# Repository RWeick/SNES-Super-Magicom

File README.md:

# SNES-Super-Magicom
The Kicad files for the SNES Super Magicom

PCB Thicknesses: 
Mainboard - 1.6 mm
RAM Board - 1.6 mm
System Connector Board - 1.2 mm

The system connector board has been modified to allow for the HiROM mod to be installed. Jumpers are labeled to facilitate operation with or without the mod.

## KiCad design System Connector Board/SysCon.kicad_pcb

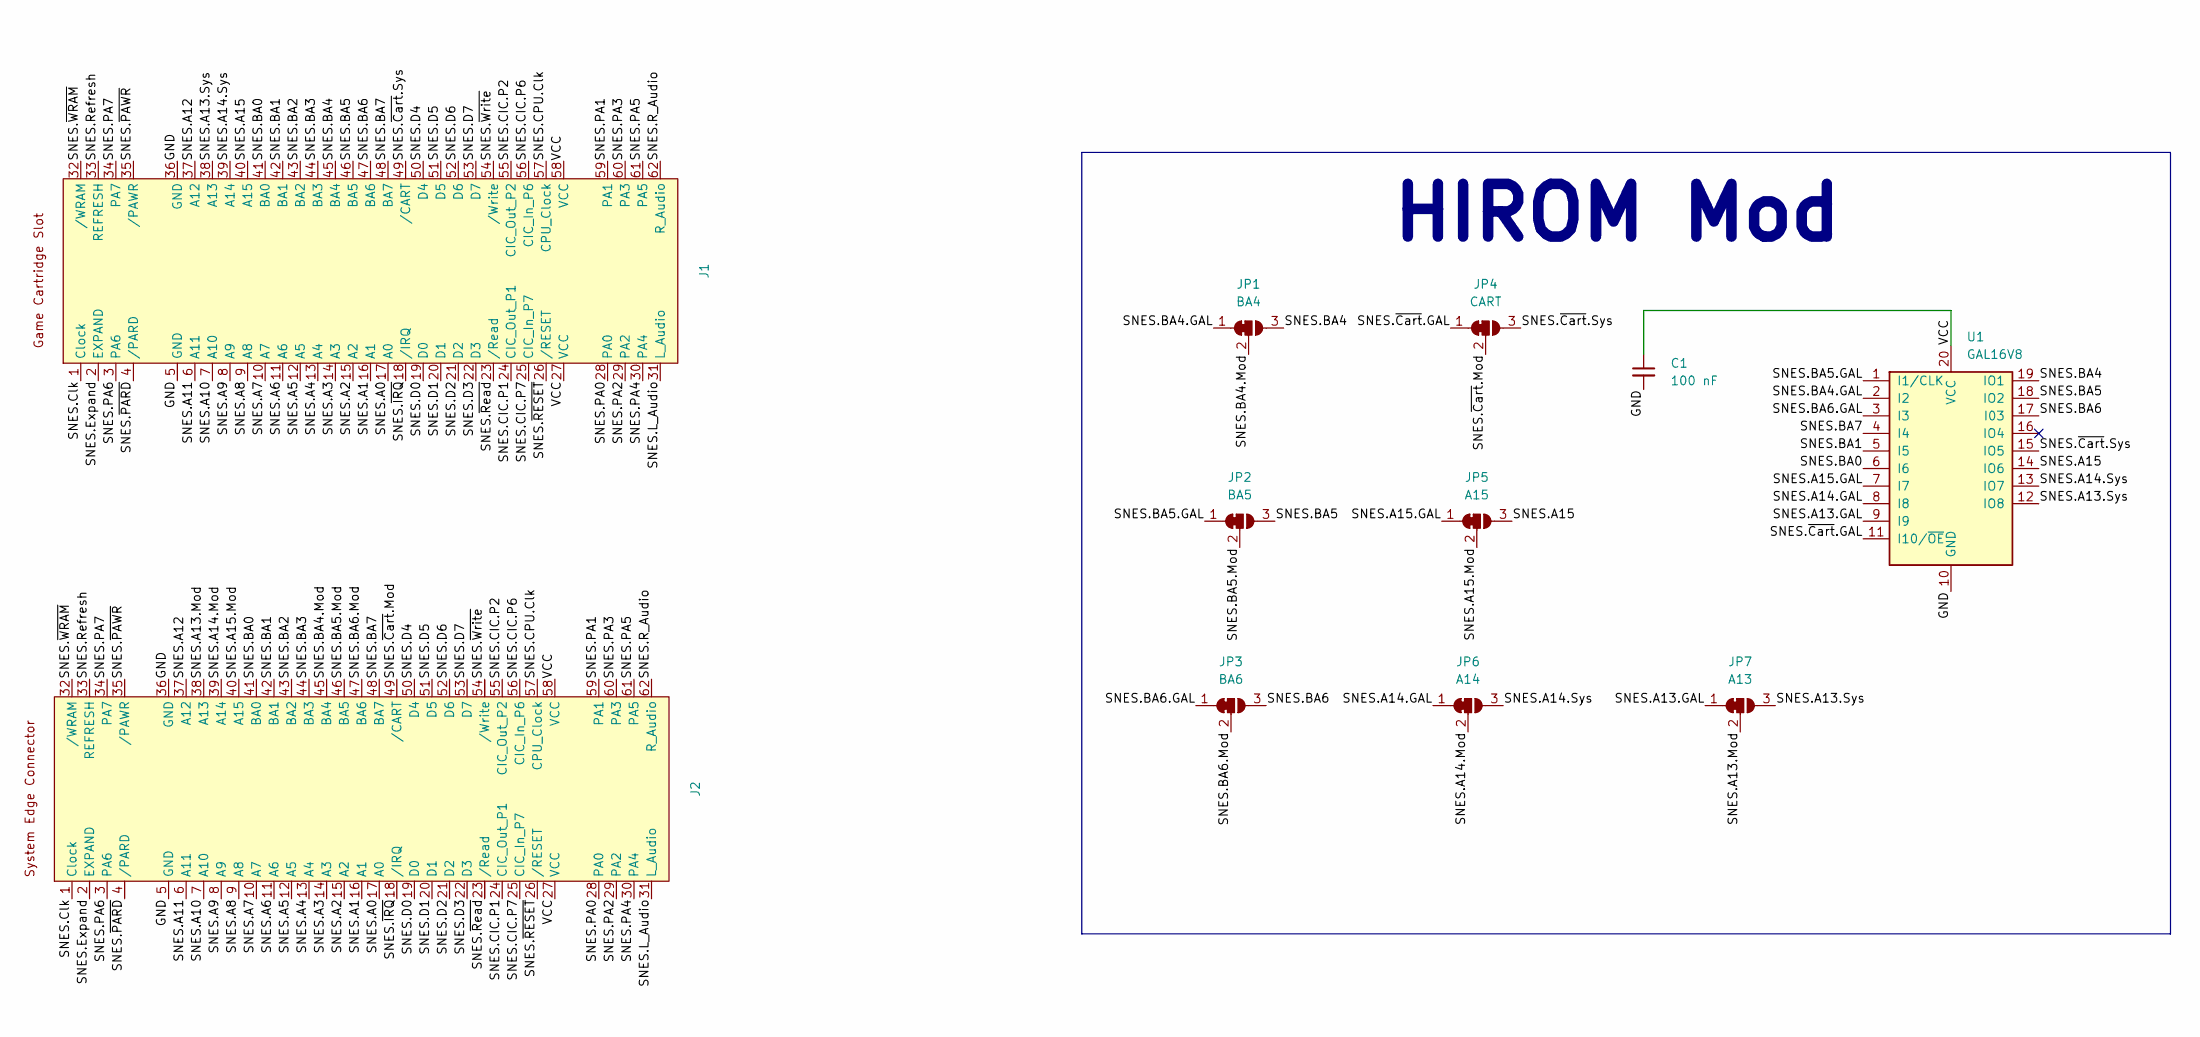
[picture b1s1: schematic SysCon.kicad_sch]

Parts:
C1: 100 nF; C_Disc_D4.3mm_W1.9mm_P5.00mm
J1: Top Connector
J2: Bottom Connector
JP1: BA4; SolderJumper-3_P1.3mm_Open_RoundedPad1.0x1.5mm_NumberLabels
JP2: BA5; SolderJumper-3_P1.3mm_Open_RoundedPad1.0x1.5mm_NumberLabels
JP3: BA6; SolderJumper-3_P1.3mm_Open_RoundedPad1.0x1.5mm_NumberLabels
JP4: CART; SolderJumper-3_P1.3mm_Open_RoundedPad1.0x1.5mm_NumberLabels
JP5: A15; SolderJumper-3_P1.3mm_Open_RoundedPad1.0x1.5mm_NumberLabels
JP6: A14; SolderJumper-3_P1.3mm_Open_RoundedPad1.0x1.5mm_NumberLabels
JP7: A13; SolderJumper-3_P1.3mm_Open_RoundedPad1.0x1.5mm_NumberLabels
U1: GAL16V8; DIP-20_W7.62mm

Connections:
/GND: C1.2, J1.5 (GND), J1.36 (GND), J2.5 (GND), J2.36 (GND), U1.10 (GND)
/SNES.A0: J1.17 (A0), J2.17 (A0)
/SNES.A1: J1.16 (A1), J2.16 (A1)
/SNES.A2: J1.15 (A2), J2.15 (A2)
/SNES.A3: J1.14 (A3), J2.14 (A3)
/SNES.A4: J1.13 (A4), J2.13 (A4)
/SNES.A5: J1.12 (A5), J2.12 (A5)
/SNES.A6: J1.11 (A6), J2.11 (A6)
/SNES.A7: J1.10 (A7), J2.10 (A7)
/SNES.A8: J1.9 (A8), J2.9 (A8)
/SNES.A9: J1.8 (A9), J2.8 (A9)
/SNES.A10: J1.7 (A10), J2.7 (A10)
/SNES.A11: J1.6 (A11), J2.6 (A11)
/SNES.A12: J1.37 (A12), J2.37 (A12)
/SNES.A13.GAL: JP7.1 (A), U1.9 (I9)
/SNES.A13.Mod: J2.38 (A13), JP7.2 (C)
/SNES.A13.Sys: J1.38 (A13), JP7.3 (B), U1.12 (IO8)
/SNES.A14.GAL: JP6.1 (A), U1.8 (I8)
/SNES.A14.Mod: J2.39 (A14), JP6.2 (C)
/SNES.A14.Sys: J1.39 (A14), JP6.3 (B), U1.13 (IO7)
/SNES.A15: J1.40 (A15), JP5.3 (B), U1.14 (IO6)
/SNES.A15.GAL: JP5.1 (A), U1.7 (I7)
/SNES.A15.Mod: J2.40 (A15), JP5.2 (C)
/SNES.BA0: J1.41 (BA0), J2.41 (BA0), U1.6 (I6)
/SNES.BA1: J1.42 (BA1), J2.42 (BA1), U1.5 (I5)
/SNES.BA2: J1.43 (BA2), J2.43 (BA2)
/SNES.BA3: J1.44 (BA3), J2.44 (BA3)
/SNES.BA4: J1.45 (BA4), JP1.3 (B), U1.19 (IO1)
/SNES.BA4.GAL: JP1.1 (A), U1.2 (I2)
/SNES.BA4.Mod: J2.45 (BA4), JP1.2 (C)
/SNES.BA5: J1.46 (BA5), JP2.3 (B), U1.18 (IO2)
/SNES.BA5.GAL: JP2.1 (A), U1.1 (I1/CLK)
/SNES.BA5.Mod: J2.46 (BA5), JP2.2 (C)
/SNES.BA6: J1.47 (BA6), JP3.3 (B), U1.17 (I03)
/SNES.BA6.GAL: JP3.1 (A), U1.3 (I3)
/SNES.BA6.Mod: J2.47 (BA6), JP3.2 (C)
/SNES.BA7: J1.48 (BA7), J2.48 (BA7), U1.4 (I4)
/SNES.CIC.P1: J1.24 (CIC_Out_P1), J2.24 (CIC_Out_P1)
/SNES.CIC.P2: J1.55 (CIC_Out_P2), J2.55 (CIC_Out_P2)
/SNES.CIC.P6: J1.56 (CIC_In_P6), J2.56 (CIC_In_P6)
/SNES.CIC.P7: J1.25 (CIC_In_P7), J2.25 (CIC_In_P7)
/SNES.CPU.Clk: J1.57 (CPU_Clock), J2.57 (CPU_Clock)
/SNES.Clk: J1.1 (Clock), J2.1 (Clock)
/SNES.D0: J1.19 (D0), J2.19 (D0)
/SNES.D1: J1.20 (D1), J2.20 (D1)
/SNES.D2: J1.21 (D2), J2.21 (D2)
/SNES.D3: J1.22 (D3), J2.22 (D3)
/SNES.D4: J1.50 (D4), J2.50 (D4)
/SNES.D5: J1.51 (D5), J2.51 (D5)
/SNES.D6: J1.52 (D6), J2.52 (D6)
/SNES.D7: J1.53 (D7), J2.53 (D7)
/SNES.Expand: J1.2 (EXPAND), J2.2 (EXPAND)
/SNES.L_Audio: J1.31 (L_Audio), J2.31 (L_Audio)
/SNES.PA0: J1.28 (PA0), J2.28 (PA0)
/SNES.PA1: J1.59 (PA1), J2.59 (PA1)
/SNES.PA2: J1.29 (PA2), J2.29 (PA2)
/SNES.PA3: J1.60 (PA3), J2.60 (PA3)
/SNES.PA4: J1.30 (PA4), J2.30 (PA4)
/SNES.PA5: J1.61 (PA5), J2.61 (PA5)
/SNES.PA6: J1.3 (PA6), J2.3 (PA6)
/SNES.PA7: J1.34 (PA7), J2.34 (PA7)
/SNES.R_Audio: J1.62 (R_Audio), J2.62 (R_Audio)
/SNES.Refresh: J1.33 (REFRESH), J2.33 (REFRESH)
/SNES.~Cart.GAL: JP4.1 (A), U1.11 (I10/~OE)
/SNES.~Cart.Mod: J2.49 (/CART), JP4.2 (C)
/SNES.~Cart.Sys: J1.49 (/CART), JP4.3 (B), U1.15 (IO5)
/SNES.~IRQ: J1.18 (/IRQ), J2.18 (/IRQ)
/SNES.~PARD: J1.4 (/PARD), J2.4 (/PARD)
/SNES.~PAWR: J1.35 (/PAWR), J2.35 (/PAWR)
/SNES.~RESET: J1.26 (/RESET), J2.26 (/RESET)
/SNES.~Read: J1.23 (/Read), J2.23 (/Read)
/SNES.~WRAM: J1.32 (/WRAM), J2.32 (/WRAM)
/SNES.~Write: J1.54 (/Write), J2.54 (/Write)
/VCC: C1.1, J1.27 (VCC), J1.58 (VCC), J2.27 (VCC), J2.58 (VCC), U1.20 (VCC)

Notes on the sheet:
HIROM Mod

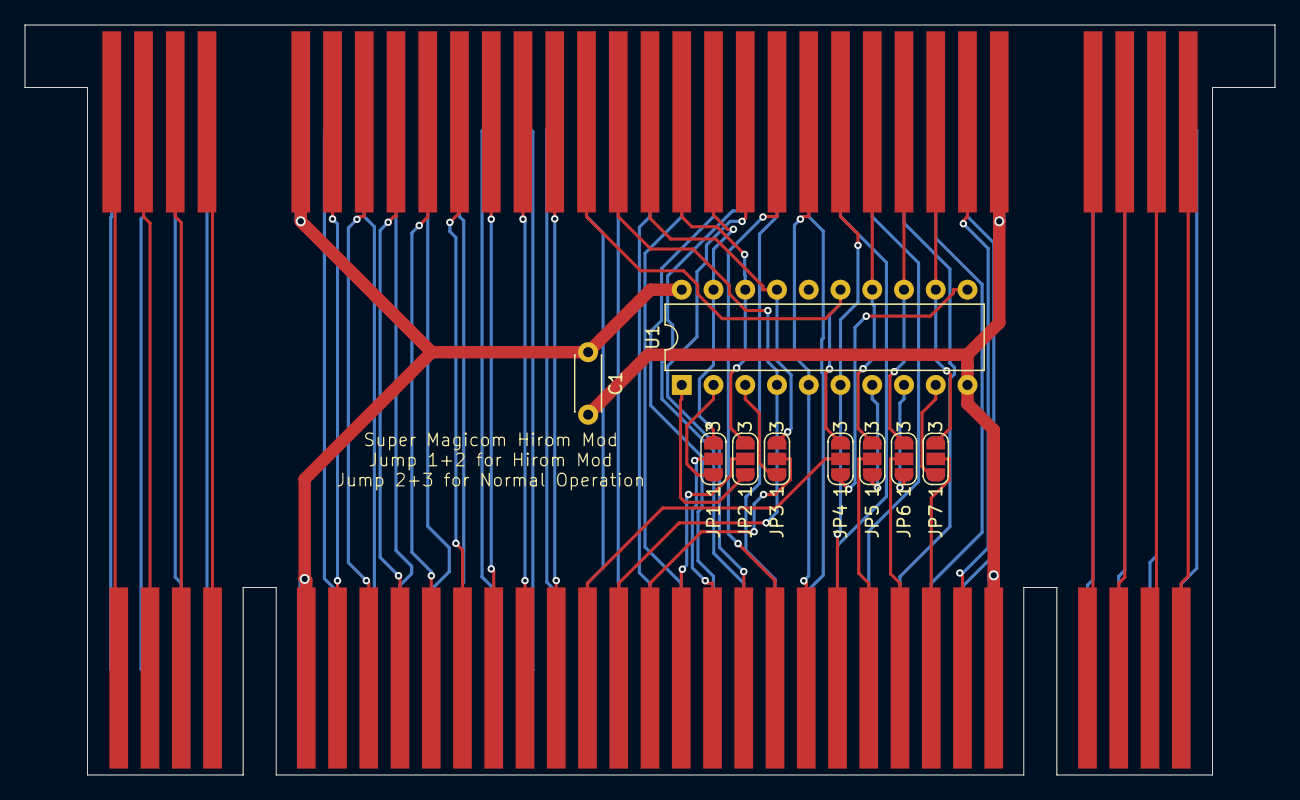
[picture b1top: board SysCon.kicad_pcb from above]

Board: 2 copper layers, 100.0 x 60.0 mm, 11 parts (0 on the bottom side), 74 nets.

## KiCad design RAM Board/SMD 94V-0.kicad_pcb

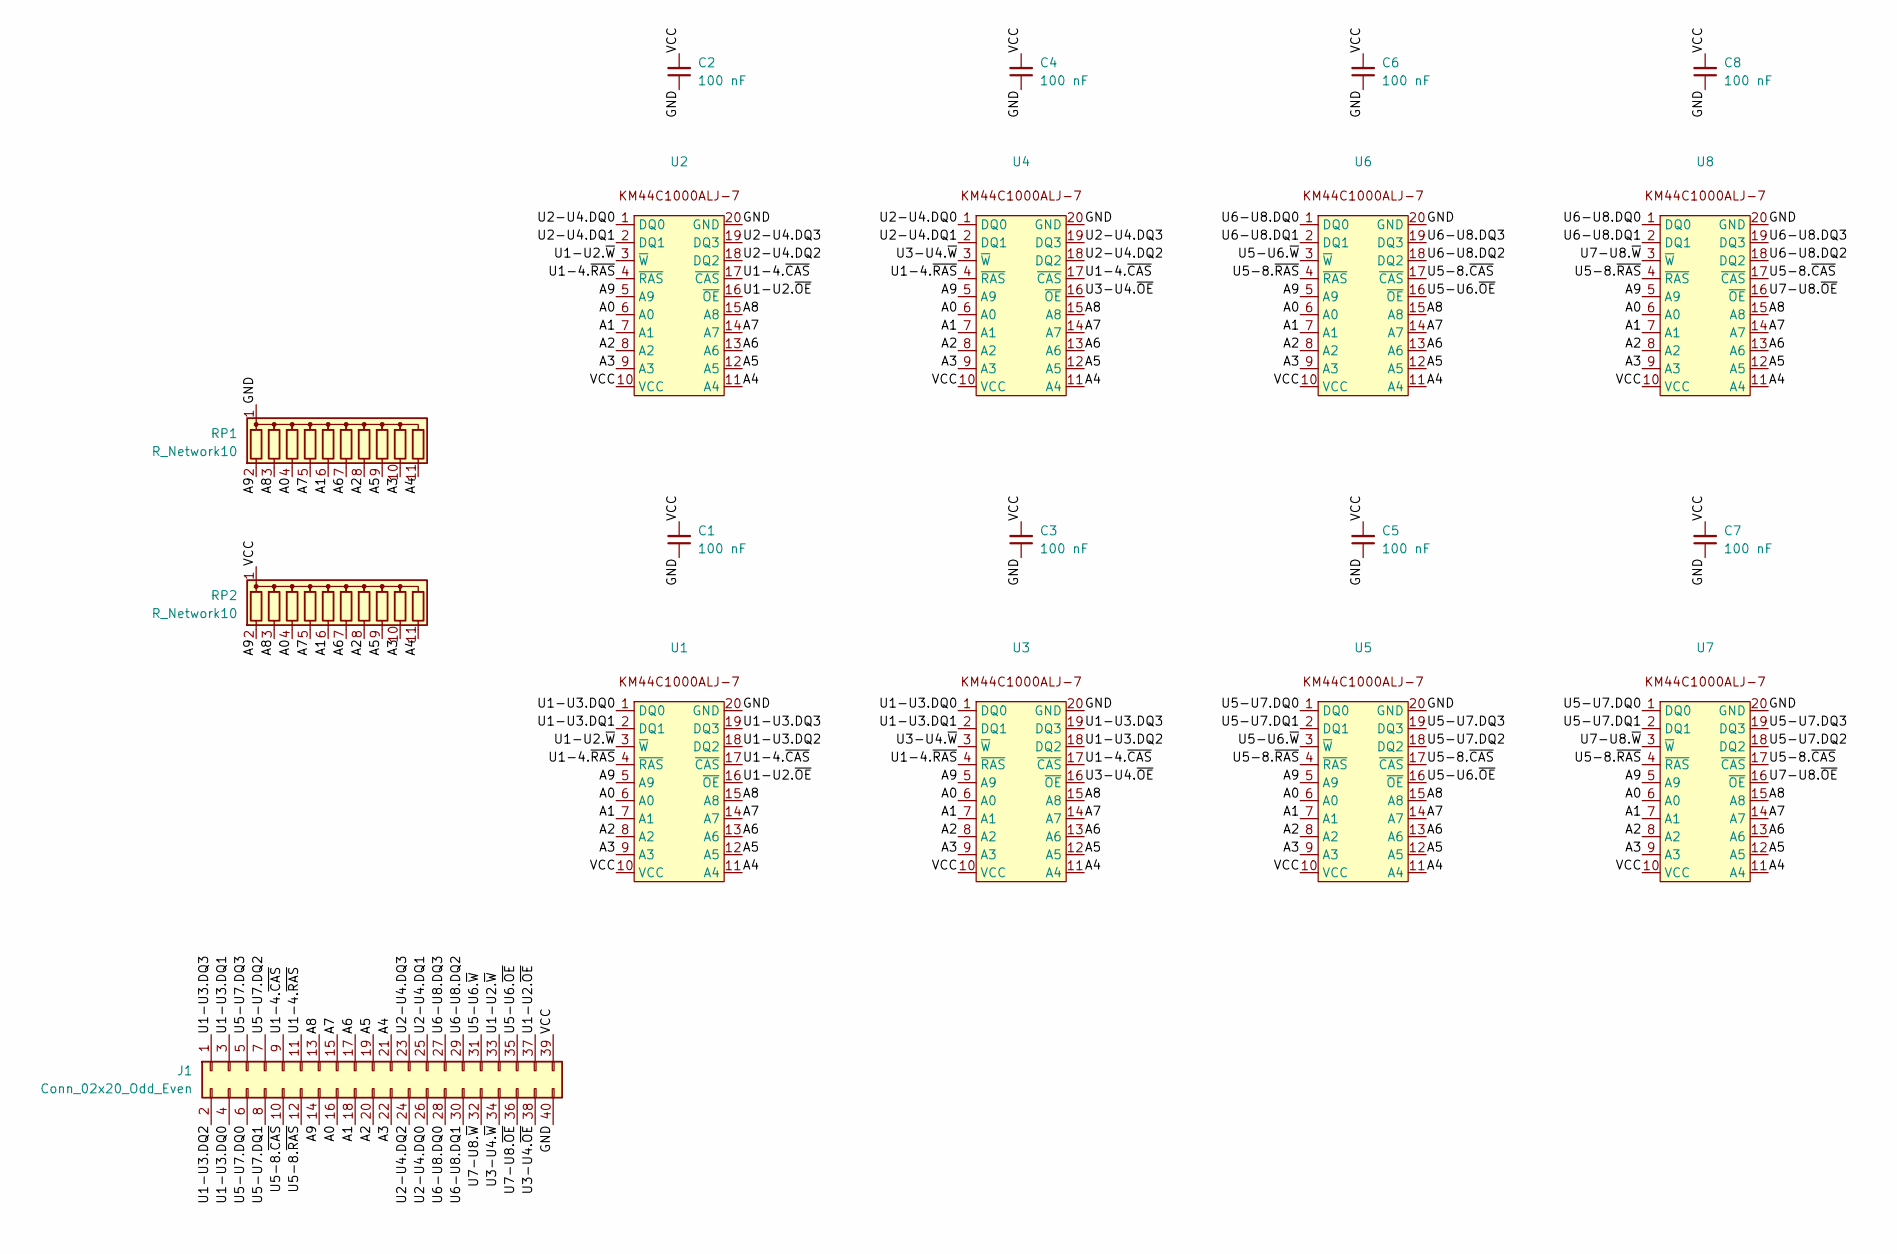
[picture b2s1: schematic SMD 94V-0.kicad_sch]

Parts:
C1, C2, C3, C4, C5, C6, C7, C8: 100 nF; Capacitor
J1: Conn_02x20_Odd_Even; PinHeader_2x20_P2.54mm_Vertical
RP1, RP2: R_Network10; R_Array_SIP11
U1, U2, U3, U4, U5, U6, U7, U8: KM44C1000ALJ-7

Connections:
/A0: J1.16, RP1.4 (R3), RP2.4 (R3), U1.6 (A0), U2.6 (A0), U3.6 (A0), U4.6 (A0), U5.6 (A0), U6.6 (A0), U7.6 (A0), U8.6 (A0)
/A1: J1.18, RP1.6 (R5), RP2.6 (R5), U1.7 (A1), U2.7 (A1), U3.7 (A1), U4.7 (A1), U5.7 (A1), U6.7 (A1), U7.7 (A1), U8.7 (A1)
/A2: J1.20, RP1.8 (R7), RP2.8 (R7), U1.8 (A2), U2.8 (A2), U3.8 (A2), U4.8 (A2), U5.8 (A2), U6.8 (A2), U7.8 (A2), U8.8 (A2)
/A3: J1.22, RP1.10 (R9), RP2.10 (R9), U1.9 (A3), U2.9 (A3), U3.9 (A3), U4.9 (A3), U5.9 (A3), U6.9 (A3), U7.9 (A3), U8.9 (A3)
/A4: J1.21, RP1.11 (R10), RP2.11 (R10), U1.11 (A4), U2.11 (A4), U3.11 (A4), U4.11 (A4), U5.11 (A4), U6.11 (A4), U7.11 (A4), U8.11 (A4)
/A5: J1.19, RP1.9 (R8), RP2.9 (R8), U1.12 (A5), U2.12 (A5), U3.12 (A5), U4.12 (A5), U5.12 (A5), U6.12 (A5), U7.12 (A5), U8.12 (A5)
/A6: J1.17, RP1.7 (R6), RP2.7 (R6), U1.13 (A6), U2.13 (A6), U3.13 (A6), U4.13 (A6), U5.13 (A6), U6.13 (A6), U7.13 (A6), U8.13 (A6)
/A7: J1.15, RP1.5 (R4), RP2.5 (R4), U1.14 (A7), U2.14 (A7), U3.14 (A7), U4.14 (A7), U5.14 (A7), U6.14 (A7), U7.14 (A7), U8.14 (A7)
/A8: J1.13, RP1.3 (R2), RP2.3 (R2), U1.15 (A8), U2.15 (A8), U3.15 (A8), U4.15 (A8), U5.15 (A8), U6.15 (A8), U7.15 (A8), U8.15 (A8)
/A9: J1.14, RP1.2 (R1), RP2.2 (R1), U1.5 (A9), U2.5 (A9), U3.5 (A9), U4.5 (A9), U5.5 (A9), U6.5 (A9), U7.5 (A9), U8.5 (A9)
/GND: C1.1, C2.1, C3.1, C4.1, C5.1, C6.1, C7.1, C8.1, J1.40, RP1.1 (common), U1.20 (GND), U2.20 (GND), U3.20 (GND), U4.20 (GND), U5.20 (GND), U6.20 (GND), U7.20 (GND), U8.20 (GND)
/U1-4.~CAS: J1.9, U1.17 (~CAS), U2.17 (~CAS), U3.17 (~CAS), U4.17 (~CAS)
/U1-4.~RAS: J1.11, U1.4 (~RAS), U2.4 (~RAS), U3.4 (~RAS), U4.4 (~RAS)
/U1-U2.~OE: J1.37, U1.16 (~OE), U2.16 (~OE)
/U1-U2.~W: J1.33, U1.3 (~W), U2.3 (~W)
/U1-U3.DQ0: J1.4, U1.1 (DQ0), U3.1 (DQ0)
/U1-U3.DQ1: J1.3, U1.2 (DQ1), U3.2 (DQ1)
/U1-U3.DQ2: J1.2, U1.18 (DQ2), U3.18 (DQ2)
/U1-U3.DQ3: J1.1, U1.19 (DQ3), U3.19 (DQ3)
/U2-U4.DQ0: J1.26, U2.1 (DQ0), U4.1 (DQ0)
/U2-U4.DQ1: J1.25, U2.2 (DQ1), U4.2 (DQ1)
/U2-U4.DQ2: J1.24, U2.18 (DQ2), U4.18 (DQ2)
/U2-U4.DQ3: J1.23, U2.19 (DQ3), U4.19 (DQ3)
/U3-U4.~OE: J1.38, U3.16 (~OE), U4.16 (~OE)
/U3-U4.~W: J1.34, U3.3 (~W), U4.3 (~W)
/U5-8.~CAS: J1.10, U5.17 (~CAS), U6.17 (~CAS), U7.17 (~CAS), U8.17 (~CAS)
/U5-8.~RAS: J1.12, U5.4 (~RAS), U6.4 (~RAS), U7.4 (~RAS), U8.4 (~RAS)
/U5-U6.~OE: J1.35, U5.16 (~OE), U6.16 (~OE)
/U5-U6.~W: J1.31, U5.3 (~W), U6.3 (~W)
/U5-U7.DQ0: J1.6, U5.1 (DQ0), U7.1 (DQ0)
/U5-U7.DQ1: J1.8, U5.2 (DQ1), U7.2 (DQ1)
/U5-U7.DQ2: J1.7, U5.18 (DQ2), U7.18 (DQ2)
/U5-U7.DQ3: J1.5, U5.19 (DQ3), U7.19 (DQ3)
/U6-U8.DQ0: J1.28, U6.1 (DQ0), U8.1 (DQ0)
/U6-U8.DQ1: J1.30, U6.2 (DQ1), U8.2 (DQ1)
/U6-U8.DQ2: J1.29, U6.18 (DQ2), U8.18 (DQ2)
/U6-U8.DQ3: J1.27, U6.19 (DQ3), U8.19 (DQ3)
/U7-U8.~OE: J1.36, U7.16 (~OE), U8.16 (~OE)
/U7-U8.~W: J1.32, U7.3 (~W), U8.3 (~W)
/VCC: C1.2, C2.2, C3.2, C4.2, C5.2, C6.2, C7.2, C8.2, J1.39, RP2.1 (common), U1.10 (VCC), U2.10 (VCC), U3.10 (VCC), U4.10 (VCC), U5.10 (VCC), U6.10 (VCC), U7.10 (VCC), U8.10 (VCC)

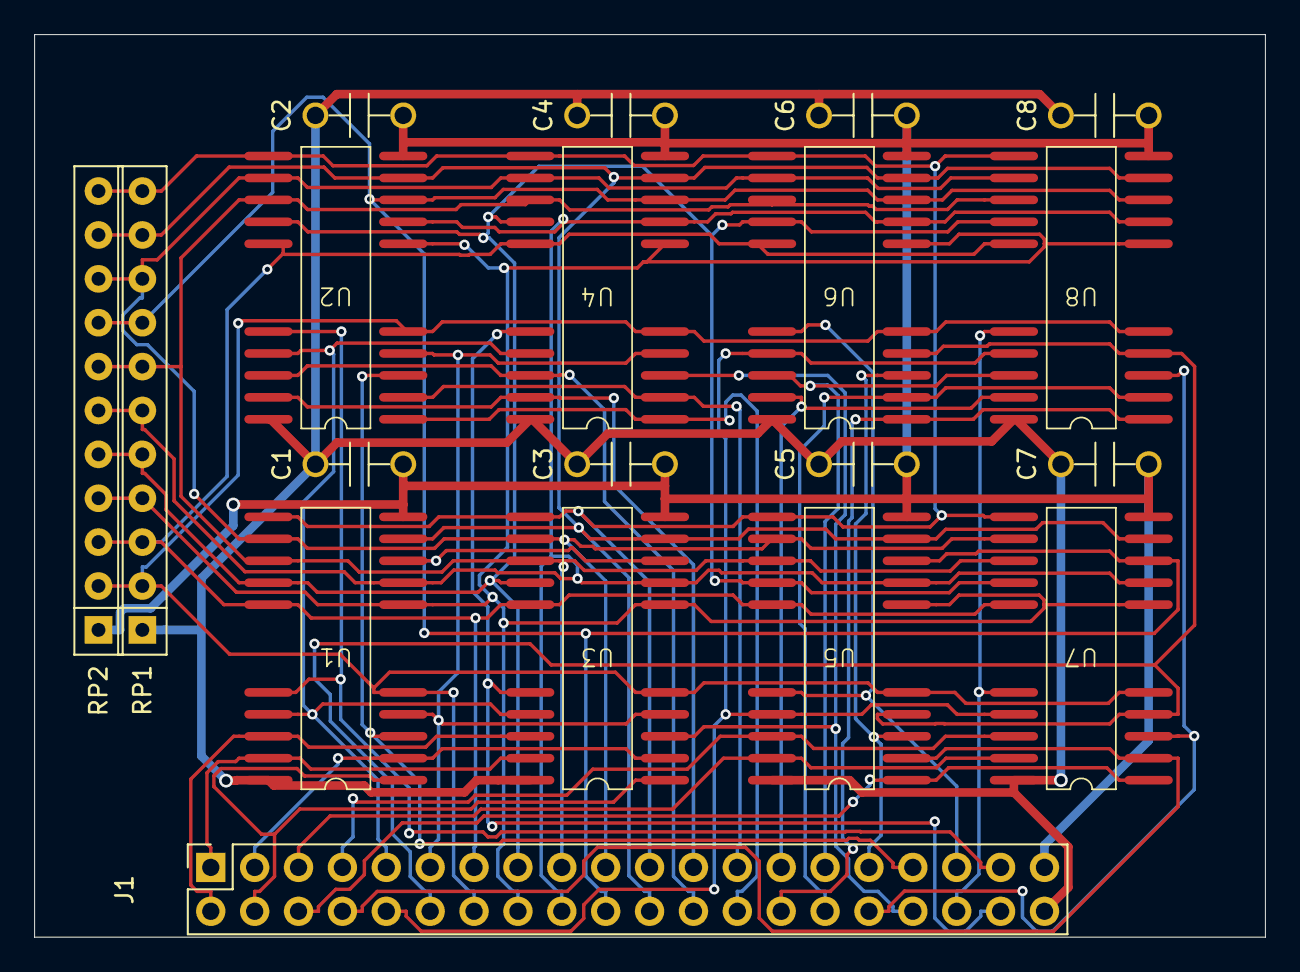
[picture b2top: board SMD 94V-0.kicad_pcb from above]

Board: 2 copper layers, 71.3 x 52.2 mm, 19 parts (0 on the bottom side), 40 nets.
